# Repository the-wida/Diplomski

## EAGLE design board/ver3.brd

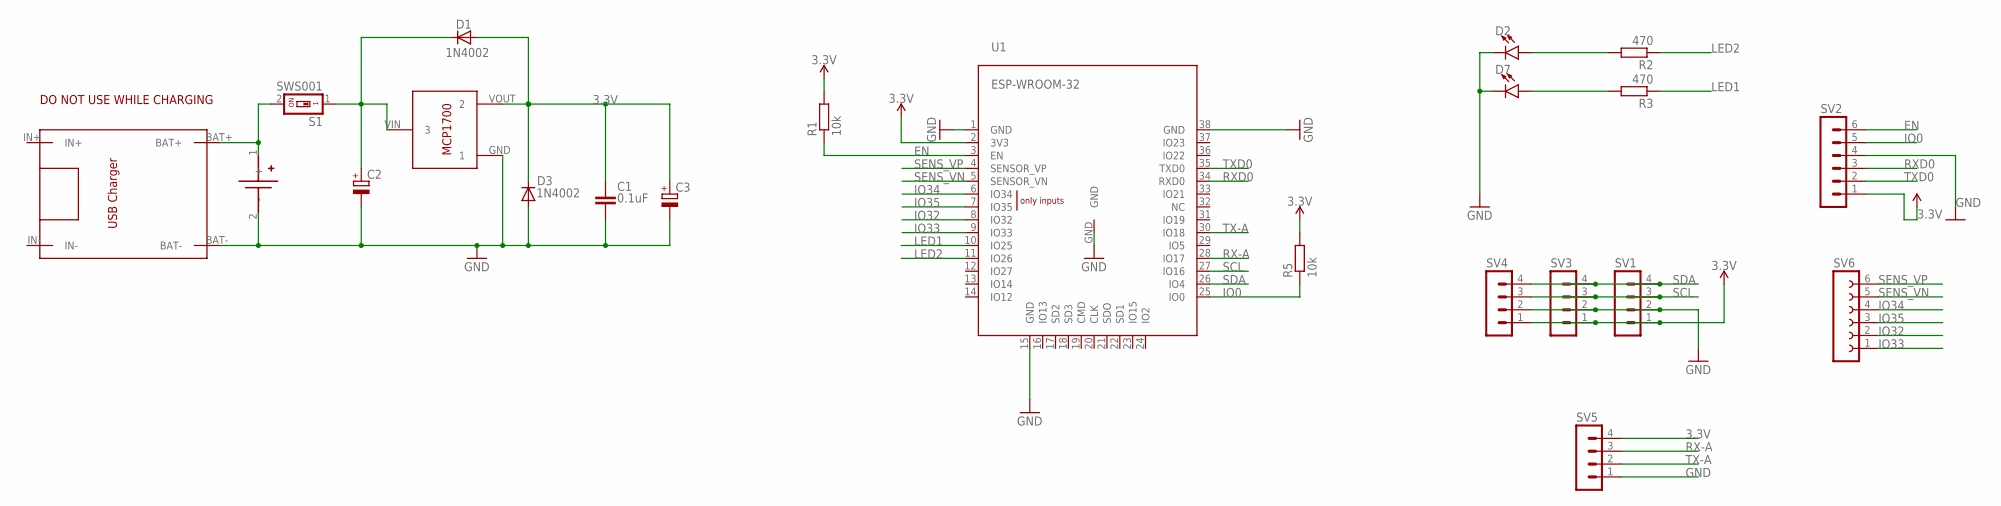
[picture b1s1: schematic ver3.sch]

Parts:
C1: 0.1uF; C075-052X106
C2, C3: CPOL-EU085CS-1AR; 085CS_1AR
D1, D3: 1N4002; DO41-10
D2, D7: LED-3MM-NO_SILK; LED_3MM-NS
R1, R5: 10k; R0603
R2, R3: 470; R0603
S1: SWS001; SMS-001
SV1, SV3, SV4, SV5: MA04-1
SV2: MA06-1
SV6: FE06-1; FE06
U1: ESP-WROOM-32
U$1: BLOSSOM-BLM-18650-1PCS
U$2: TP4056
U$3: MCP1700T-3302E/TT

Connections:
3.3V: C1.1, C3.+, D1.A, D3.C, R1.2, R5.2, SV1.1, SV2.1, SV3.1, SV4.1, SV5.4, U1.2 (3V3), U$3.VOUT (2)
EN: R1.1, SV2.6, U1.3 (EN)
GND: C1.2, C2.-, C3.-, D2.K (C), D3.A, D7.K (C), SV1.2, SV2.4, SV3.2, SV4.2, SV5.1, U1.1 (GND), U1.15 (GND), U1.38 (GND), U1.GND, U$1.2 (-), U$2.BAT-, U$3.GND (1)
GREEN-A: D7.A, R3.2
IO0: R5.1, SV2.5, U1.25 (IO0)
IO32: SV6.2, U1.8 (IO32)
IO33: SV6.1, U1.9 (IO33)
IO34: SV6.4, U1.6 (IO34)
IO35: SV6.3, U1.7 (IO35)
LED1: R3.1, U1.10 (IO25)
LED2: R2.1, U1.11 (IO26)
unnamed: S1.2, U$1.1 (+), U$2.BAT+
RX-A: SV5.3, U1.28 (IO17)
RXD0: SV2.3, U1.34 (RXD0)
SCL: SV1.3, SV3.3, SV4.3, U1.27 (IO16)
SDA: SV1.4, SV3.4, SV4.4, U1.26 (IO4)
SENS_VN: SV6.5, U1.5 (SENSOR_VN)
SENS_VP: SV6.6, U1.4 (SENSOR_VP)
TX-A: SV5.2, U1.30 (IO18)
TXD0: SV2.2, U1.35 (TXD0)
VIN: C2.+, D1.C, S1.1, U$3.VIN (3)
YELLOW-A: D2.A, R2.2

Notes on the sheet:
DO NOT USE WHILE CHARGING

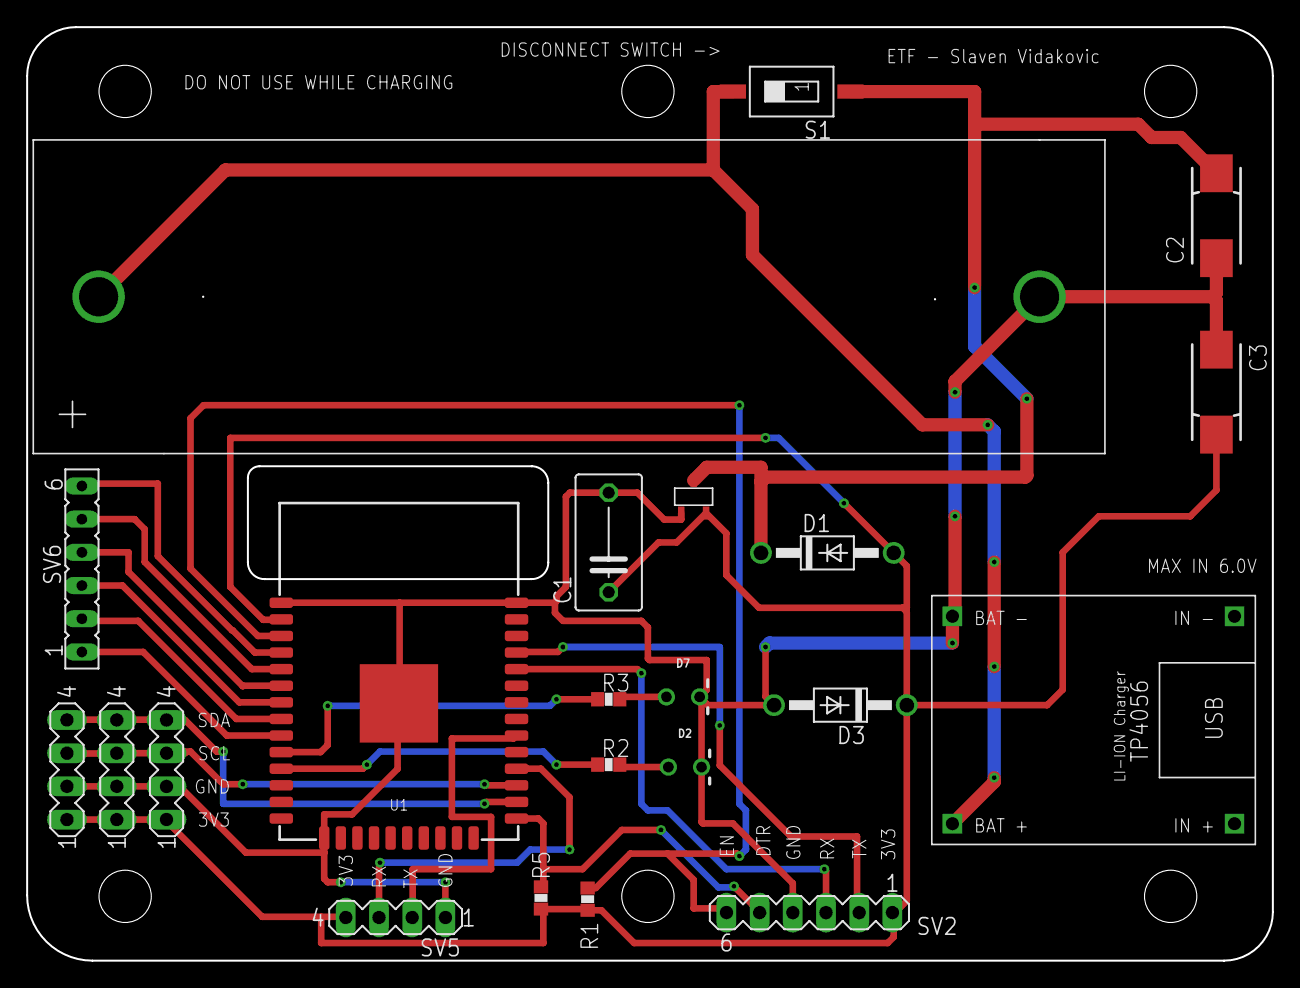
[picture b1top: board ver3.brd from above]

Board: 2 copper layers, 95.3 x 71.4 mm, 22 parts (0 on the bottom side), 22 nets.

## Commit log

2022-02-14 Update sdkconfig
2022-02-15 Update Makefile

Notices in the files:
parts and their libraries:
SparkFun-LED: Licensing: Creative Commons ShareAlike 4.0 International - https://creativecommons.org/licenses/by-sa/4.0
